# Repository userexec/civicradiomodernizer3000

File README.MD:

# Civic Radio Modernizer 3000

This package of KiCad files and an Arduino sketch produces a circuit board you don't want. It hijacks the amplifier inputs, source switching functions, and radio preset buttons/LEDs of a Honda 39100-SEO-A300-M1 radio connected to it via a parallel cable. Note that this radio does not have a parallel port (of course it doesn't). You have to chop the cable in half and solder the open end into specific points around the radio, then connect the other end to this board. Power comes over the parallel cable so it's the only required connection--just print a case for it and tuck it behind the dash anywhere it fits.

## What it adds

Attaching this board over parallel to the appropriate Honda radio with correct points soldered adds:
- Bluetooth
- Radio/Cassette/Bluetooth switching on radio preset buttons 1, 2, 3
- Bluetooth audio controls on radio preset buttons 4, 5, 6
- Funky animations of the faceplate LEDs when you press those buttons
- All audio adjustments like volume, balance, fade, bass, treble etc. retain function across all modes
- Steering wheel controls over optional DB-9 serial cable
- 3.5mm output of anything currently playing, regardless of source
- RCA output of anything currently playing, regardless of source
- Attachment via DB-9 serial cable to a controller hub for the rest of the car's modules

## What you should build instead of this

Seriously don't build this. By the time this board is printed and you've ordered components it comes up to like $150. It requires hours of soldering and a significant possibility of breaking your radio. How are you even going to use the CAT-BUS port? It uses some random undocumented protocol some weird guy on the internet put together for a project car. Why do you even have a Honda 39100-SEO-A300-M1?

A bluetooth cassette tape will work just as well. Does the cassette belt on your 39100-SEO-A300-M1 not work? A [PRB SCX 16.0 square cut belt](https://marvac.com/products/prb-scx-16-0-square-cut-belt-for-vcr-cassette-cd-drive-or-dvd-drive-scx16-0?_pos=1&_sid=dd0a25bef&_ss=r) will fit perfectly.

Better yet, buy an aftermarket amplifier with bluetooth.

If you're just looking for a way to attach an amp to your vintage radio, yes this will provide the correct outputs, but there are so many options that are million times easier.

## Pin mapping

The whole magic is in where you solder the parallel cable's wires into the radio. Here's what goes to what:

| Wire color | Pin | Function | Solder point |
| ------- | ------- | ------- | ------- |
| **brown** | **1** | GND | Radio case |
| **red** | **2** | 12V | any 12V accessory point behind main radio connector |
| **orange** | **3** | SPK_L | Bottom of main board at output of pre-amp board |
| **bad girl pink** | **4** | SPK_R | Bottom of main board at output of pre-amp board |
| **bubblegum pink** | **5** | B+ | Gray wire from main board to cassette module (disconnect wire, cut plug) |
| **princess pink** | **6** | B+RADIO | Blue wire from main board to cassette module (from same plug) |
| **yellow** | **7** | B+TAPE | Purple wire from main board to cassette module (from same plug) |
| **ninja turtle** | **8** | BTN1 | Cut traces on radio preset button board |
| **grass** | **9** | BTN2 | Solder GND to one side of switches |
| **normal blue** | **10** | BTN3 | Solder BTN inputs to other sides |
| **light blue** | **11** | BTN4 |  |
| **ugly blue (brown)** | **12** | BTN5 |  |
| **turqoise** | **13** | BTN6 |  |
| purple | 14 | GND |  |
| **normal gray** | **15** | LED6 | Cut traces on radio preset board |
| **white** | **16** | LED5 | Link all LED GNDs, solder to GND |
| **dirty white** | **17** | LED4 | Solder LED outputs to other sides |
| ***brown (white)*** | **18** | LED3 | of corresponding LEDs |
| ***orange (black)*** | **19** | LED2 |  |
| *red (black)* | 19 | LED2 |  |
| ***bubblegum pink (blue)*** | **20** | LED1 |  |
| *bad girl pink (black)* | 20 | LED1 |  |
| *princess pink (white)* | 21 |  |  |
| *yellow (black)* | 21 |  |  |
| *ninja turtle (black)* | 22 |  |  |
| *grass (brown)* | 22 |  |  |
| *light blue (black)* | 23 |  |  |
| *normal gray (black)* | 23 |  |  |
| *normal blue (white) *| 24 |  |  |
| ugly blue | 24 |  |  |
| *turqoise (green)* | 24 |  |  |
| *dirty white (green)* | 25 |  |  |
| *purple (white)* | 25 |  |  |
| white (black)* | 25 |  |  |
| disgusting gray | nc |  |  |
| *disgusting gray (green)* | nc |  |  |

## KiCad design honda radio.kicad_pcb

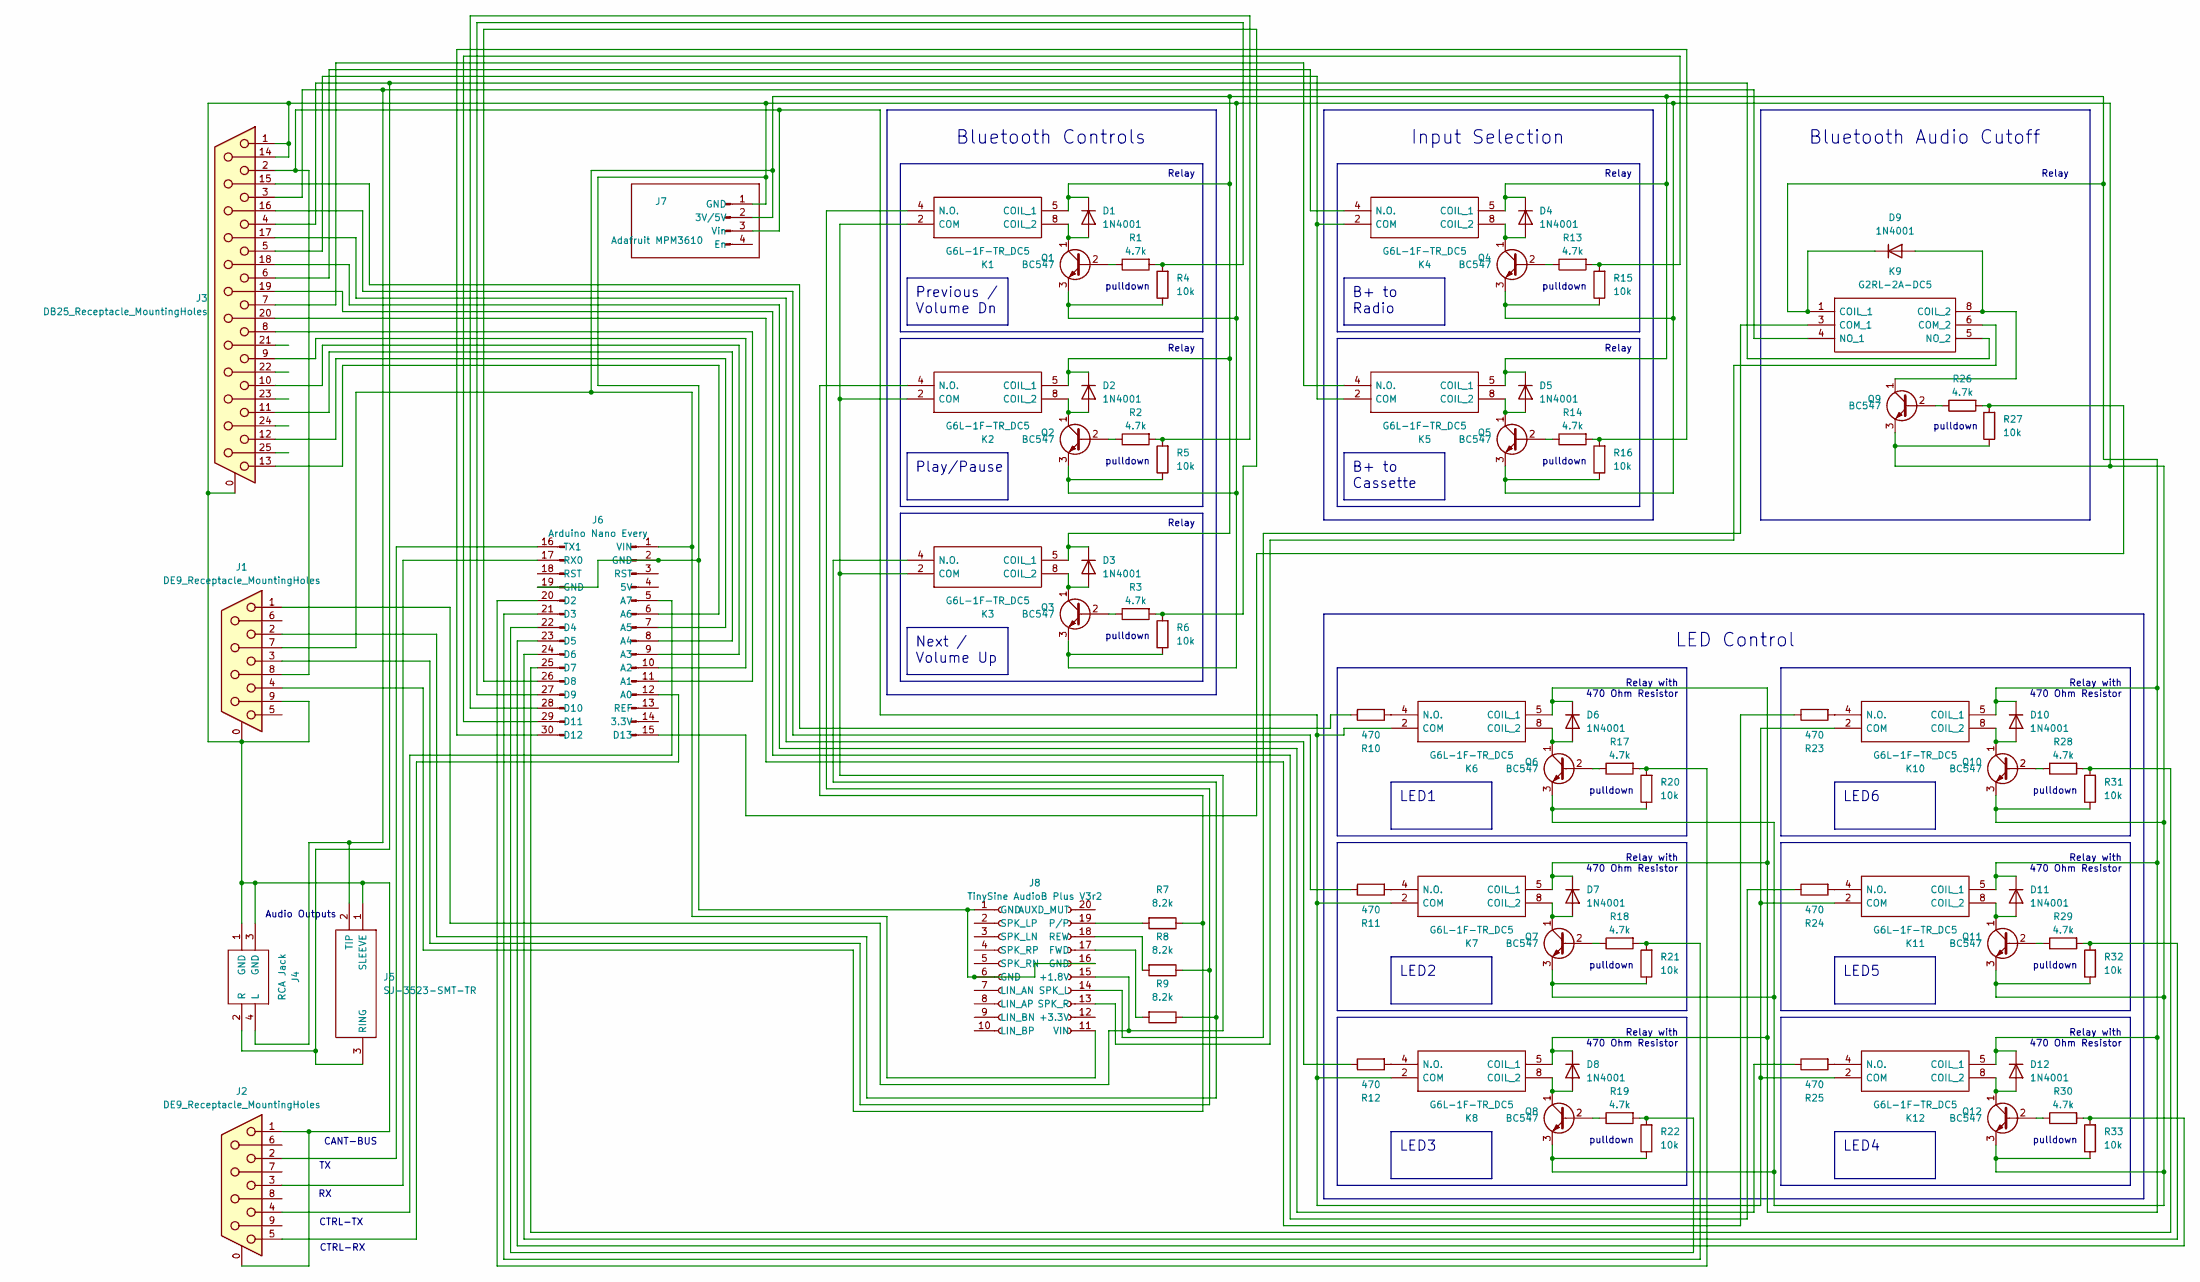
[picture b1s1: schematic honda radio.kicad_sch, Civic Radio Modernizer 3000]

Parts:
D1, D2, D3, D4, D5, D6, D7, D8, D9, D10, D11, D12: 1N4001; D_DO-41_SOD81_P10.16mm_Horizontal
J1, J2: DE9_Receptacle_MountingHoles; DB9
J3: DB25_Receptacle_MountingHoles; DB25
J4: RCA Jack; RCA jack; Mouser Part Number 490-RCJ-2112
J5: SJ-3523-SMT-TR; Audio Jack 2; Mouser Part Number 490-SJ-3523-SMT-TR
J6: Arduino Nano Every
J7: Adafruit MPM3610
J8: TinySine AudioB Plus V3r2; TinySine AudioB
K1, K2, K3, K4, K5, K6, K7, K8, K10, K11, K12: G6L-1F-TR_DC5; Omron Micro Relay; Mouser Part Number 653-G6L-1F-TRDC5
K9: G2RL-2A-DC5; G2RL2ADC12; Mouser Part Number 653-G2RL-2A-DC5
Q1, Q2, Q3, Q4, Q5, Q6, Q7, Q8, Q9, Q10, Q11, Q12: BC547; TO-92-3 Kinked Lead
R1, R2, R3, R13, R14, R17, R18, R19, R26, R28, R29, R30: 4.7k; R_Axial_DIN0207_L6.3mm_D2.5mm_P10.16mm_Horizontal
R4, R5, R6, R15, R16, R20, R21, R22, R27, R31, R32, R33: 10k; R_Axial_DIN0207_L6.3mm_D2.5mm_P10.16mm_Horizontal
R7, R8, R9: 8.2k; R_Axial_DIN0207_L6.3mm_D2.5mm_P10.16mm_Horizontal
R10, R11, R12, R23, R24, R25: 470; R_Axial_DIN0207_L6.3mm_D2.5mm_P10.16mm_Horizontal

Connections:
unnamed: D1.2 (A), K1.8 (COIL_2), Q1.1 (C)
unnamed: D1.1 (K), D2.1 (K), D3.1 (K), D4.1 (K), D5.1 (K), D6.1 (K), D7.1 (K), D8.1 (K), D9.1 (K), D10.1 (K), D11.1 (K), D12.1 (K), J1.7 (5V), J6.1 (VIN), J7.2 (3V/5V), J8.11 (VIN), K1.5 (COIL_1), K2.5 (COIL_1), K3.5 (COIL_1), K4.5 (COIL_1), K5.5 (COIL_1), K6.5 (COIL_1), K7.5 (COIL_1), K8.5 (COIL_1), K9.1 (COIL_1), K10.5 (COIL_1), K11.5 (COIL_1), K12.5 (COIL_1)
unnamed: D2.2 (A), K2.8 (COIL_2), Q2.1 (C)
unnamed: D3.2 (A), K3.8 (COIL_2), Q3.1 (C)
unnamed: D4.2 (A), K4.8 (COIL_2), Q4.1 (C)
unnamed: D5.2 (A), K5.8 (COIL_2), Q5.1 (C)
unnamed: D6.2 (A), K6.8 (COIL_2), Q6.1 (C)
unnamed: D7.2 (A), K7.8 (COIL_2), Q7.1 (C)
unnamed: D8.2 (A), K8.8 (COIL_2), Q8.1 (C)
unnamed: D9.2 (A), K9.8 (COIL_2), Q9.1 (C)
unnamed: D10.2 (A), K10.8 (COIL_2), Q10.1 (C)
unnamed: D11.2 (A), K11.8 (COIL_2), Q11.1 (C)
unnamed: D12.2 (A), K12.8 (COIL_2), Q12.1 (C)
unnamed: J1.1 (1.8V_TRIG), J8.15 (+1.8V), K1.2 (COM), K2.2 (COM), K3.2 (COM)
unnamed: J1.8 (12V), J3.2 (12V), J7.3 (Vin), K6.2 (COM), K7.2 (COM), K8.2 (COM), K10.2 (COM), K11.2 (COM), K12.2 (COM)
unnamed: J1.2 (FWD_BTN), K3.4 (N.O.), R9.1
unnamed: J1.0 (PAD), J1.9 (GND), J2.0 (PAD), J2.1 (1.8V_TRIG), J3.0 (PAD), J3.1 (GND), J3.14 (GND), J4.1 (GND), J4.3 (GND), J5.1 (SLEEVE), J6.2 (GND), J6.19 (GND), J7.1 (GND), J8.1 (GND), J8.6 (GND), J8.16 (GND), Q1.3 (E), Q2.3 (E), Q3.3 (E), Q4.3 (E), Q5.3 (E), Q6.3 (E), Q7.3 (E), Q8.3 (E), Q9.3 (E), Q10.3 (E), Q11.3 (E), Q12.3 (E), R4.1, R5.1, R6.1, R15.1, R16.1, R20.1, R21.1, R22.1, R27.1, R31.1, R32.1, R33.1
unnamed: J1.4 (PP_BTN), K2.4 (N.O.), R7.1
unnamed: J1.3 (REW_BTN), K1.4 (N.O.), R8.1
unnamed: J2.2 (FWD_BTN), J6.16 (TX1)
unnamed: J2.4 (PP_BTN), J6.5 (A7)
unnamed: J2.3 (REW_BTN), J6.17 (RX0)
unnamed: J3.5 (B+), K4.2 (COM), K5.2 (COM)
unnamed: J3.6 (B+RAD), K4.4 (N.O.)
unnamed: J3.7 (B+TAP), K5.4 (N.O.)
unnamed: J3.8 (BTN1), J6.11 (A1)
unnamed: J3.9 (BTN2), J6.10 (A2)
unnamed: J3.10 (BTN3), J6.9 (A3)
unnamed: J3.11 (BTN4), J6.8 (A4)
unnamed: J3.12 (BTN5), J6.7 (A5)
unnamed: J3.13 (BTN6), J6.6 (A6)
unnamed: J3.20 (LED1), R23.1
unnamed: J3.19 (LED2), R24.1
unnamed: J3.18 (LED3), R25.1
unnamed: J3.17 (LED4), R12.1
unnamed: J3.16 (LED5), R11.1
unnamed: J3.15 (LED6), R10.1
unnamed: J3.3 (SPK_L), J4.4 (L), J5.2 (TIP), K9.4 (NO_1)
unnamed: J3.4 (SPK_R), J4.2 (R), J5.3 (RING), K9.5 (NO_2)
unnamed: J2.5 (NC), J6.12 (A0)
unnamed: J6.20 (D2), R17.2, R20.2
unnamed: J6.21 (D3), R18.2, R21.2
unnamed: J6.22 (D4), R19.2, R22.2
unnamed: J6.23 (D5), R30.2, R33.2
unnamed: J6.24 (D6), R29.2, R32.2
unnamed: J6.25 (D7), R28.2, R31.2
unnamed: J6.26 (D8), R3.2, R6.2
unnamed: J6.27 (D9), R1.2, R4.2
unnamed: J6.28 (D10), R2.2, R5.2
unnamed: J6.29 (D11), R13.2, R15.2
unnamed: J6.30 (D12), R14.2, R16.2
unnamed: J6.15 (D13), R26.2, R27.2
unnamed: J8.17 (FWD), R9.2
unnamed: J8.19 (P/P), R7.2
unnamed: J8.18 (REW), R8.2
unnamed: J8.14 (SPK_L), K9.3 (COM_1)
unnamed: J8.13 (SPK_R), K9.6 (COM_2)
unnamed: K6.4 (N.O.), R10.2
unnamed: K7.4 (N.O.), R11.2
unnamed: K8.4 (N.O.), R12.2
unnamed: K10.4 (N.O.), R23.2
unnamed: K11.4 (N.O.), R24.2
unnamed: K12.4 (N.O.), R25.2
unnamed: Q1.2 (B), R1.1
unnamed: Q2.2 (B), R2.1
unnamed: Q3.2 (B), R3.1
unnamed: Q4.2 (B), R13.1
unnamed: Q5.2 (B), R14.1
unnamed: Q6.2 (B), R17.1
unnamed: Q7.2 (B), R18.1
unnamed: Q8.2 (B), R19.1
unnamed: Q9.2 (B), R26.1
unnamed: Q10.2 (B), R28.1
unnamed: Q11.2 (B), R29.1
unnamed: Q12.2 (B), R30.1

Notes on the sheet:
Previous / Volume Dn
Play/Pause
B+ to Radio
LED3
LED6
LED2
LED5
LED4
B+ to Cassette
LED1
Next / Volume Up
pulldown
Relay
LED Control
Audio Outputs
Relay with 470 Ohm Resistor
CTRL-TX
Bluetooth Controls
Bluetooth Audio Cutoff
CTRL-RX
Input Selection
CANT-BUS

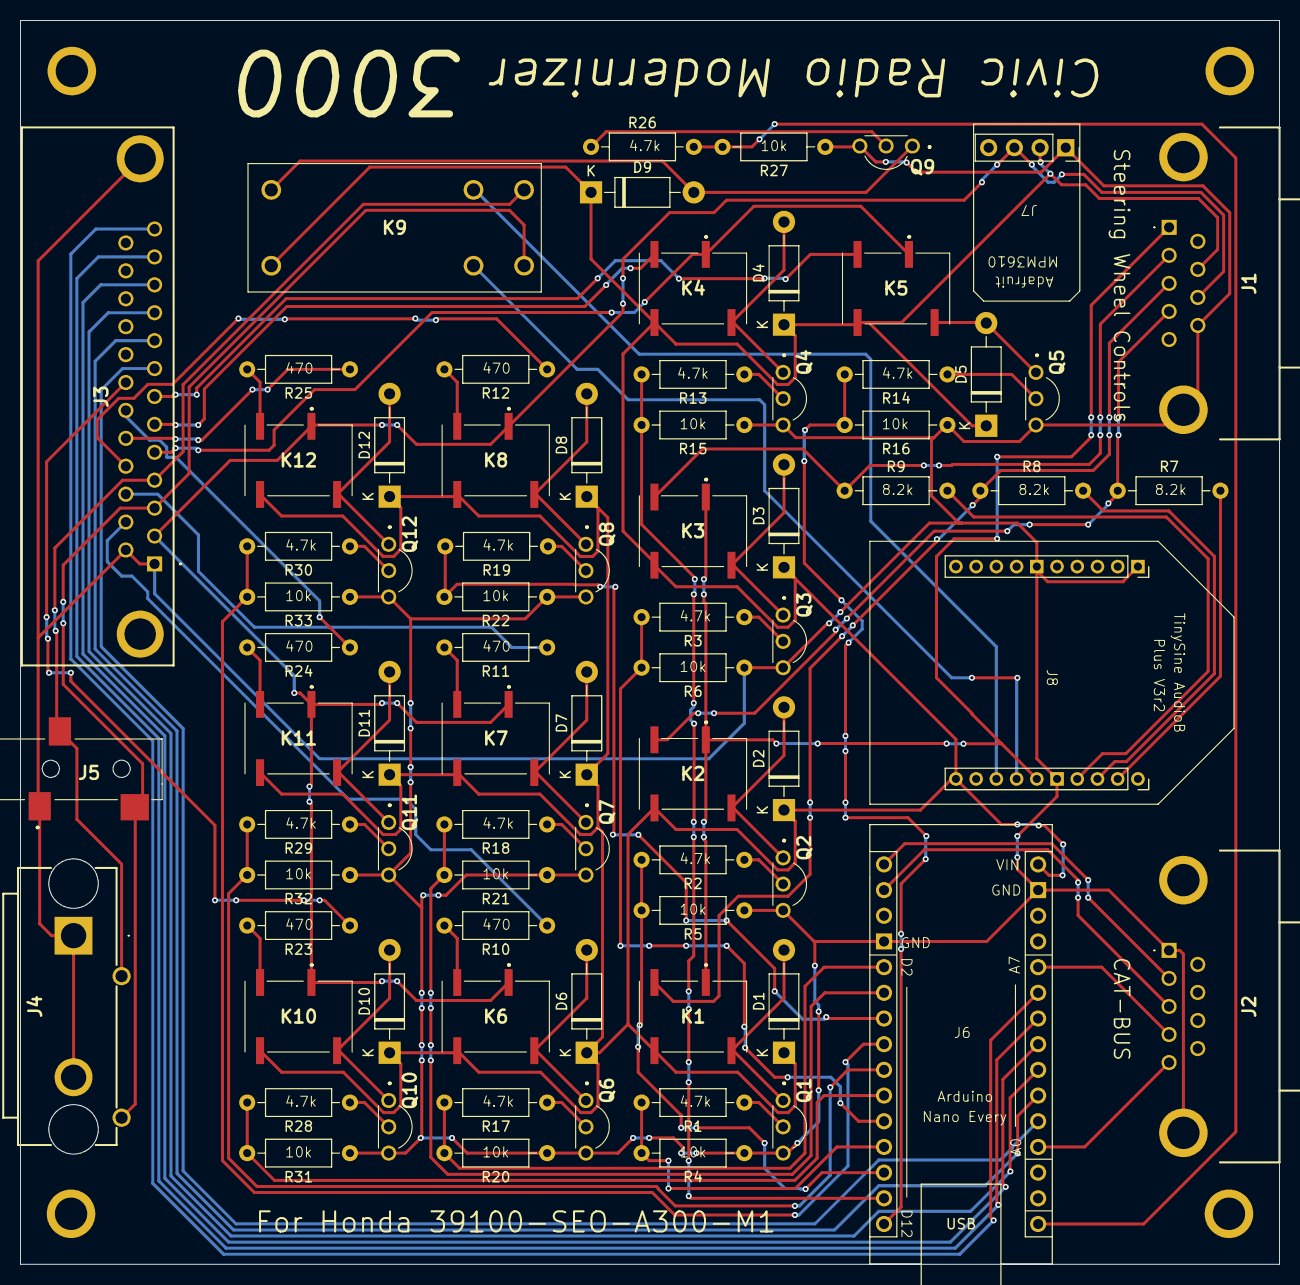
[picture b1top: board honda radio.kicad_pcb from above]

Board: 2 copper layers, 124.5 x 123.0 mm, 77 parts (0 on the bottom side), 75 nets.

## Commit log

2024-03-24 added cassette belt info
2024-03-24 added belt link
2024-03-28 added missing trace
2024-03-28 replaced photo
2024-03-28 added missing silkscreen label on R27
